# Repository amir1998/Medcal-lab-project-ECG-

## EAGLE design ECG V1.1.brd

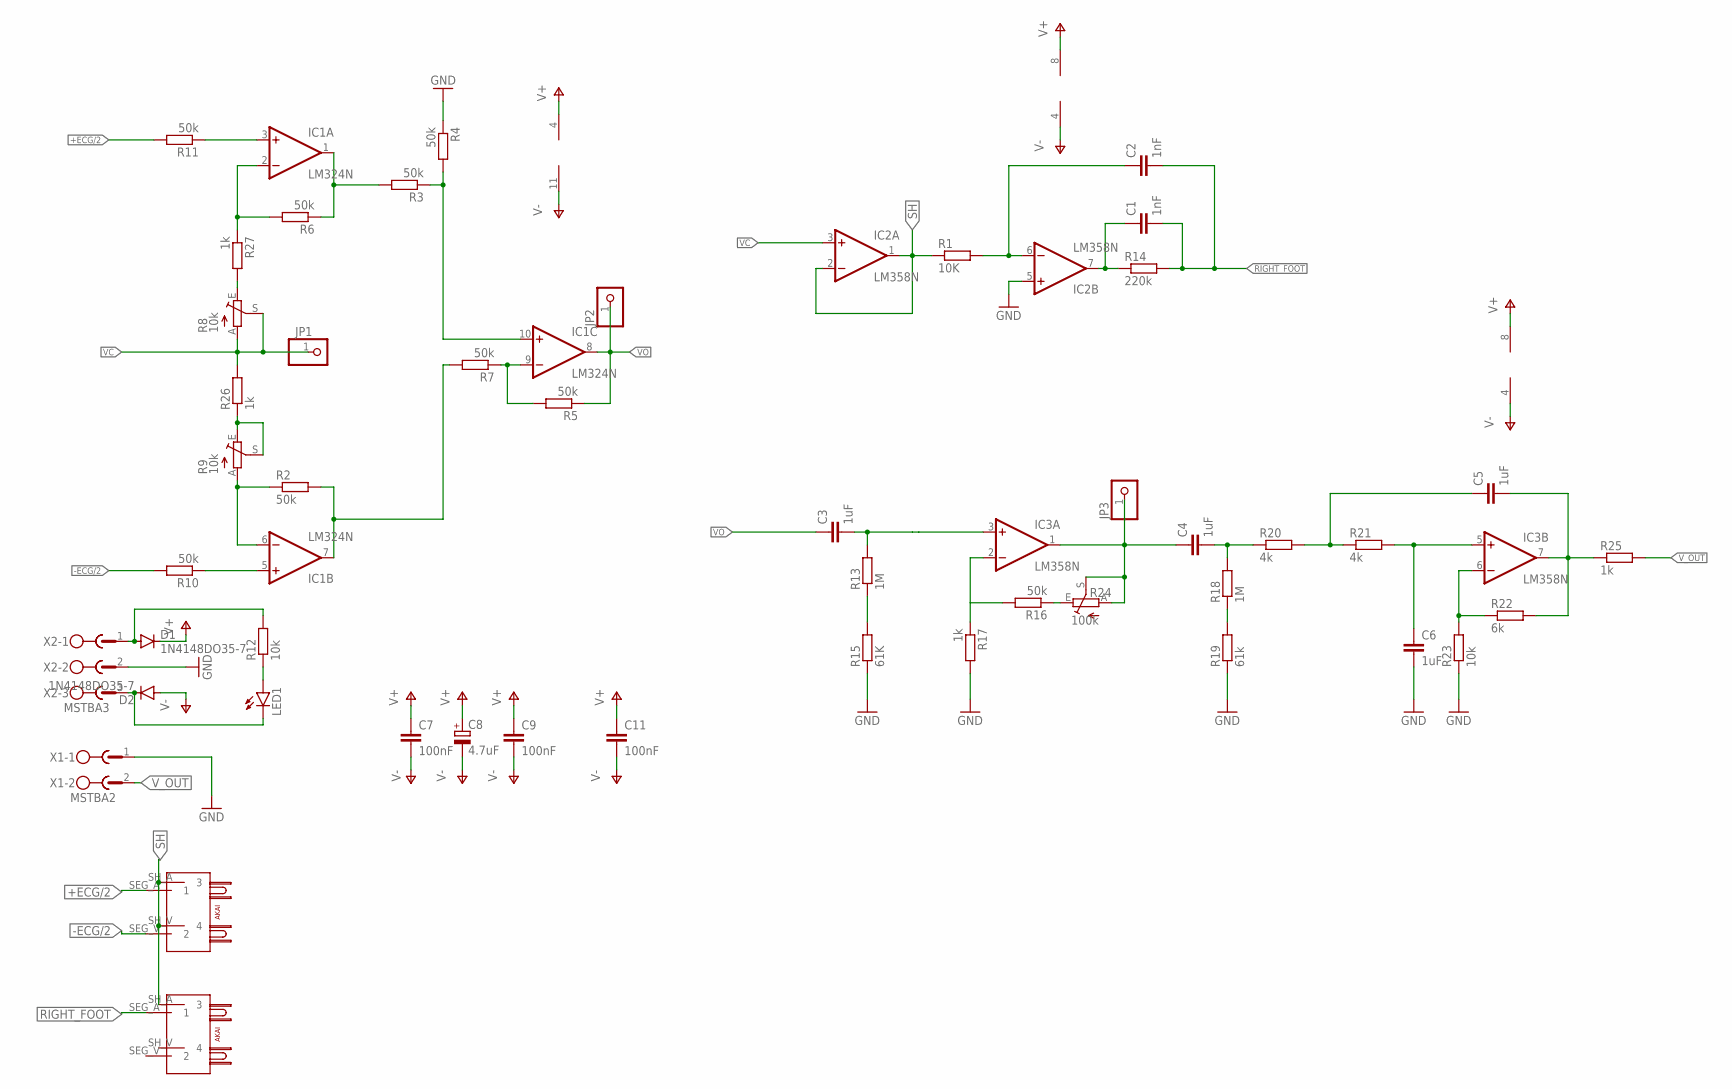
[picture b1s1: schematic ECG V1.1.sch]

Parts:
C1, C2: 1nF; C050-024X044
C3: 1uF; C075-032X103
C4, C5, C6: 1uF; C050-024X044
C7, C9, C11: 100nF; C050-024X044
C8: 4.7uF; E2-4
D1, D2: 1N4148DO35-7; DO35-7
IC1: LM324N; DIL14
IC2, IC3: LM358N; DIL08
JP1, JP2, JP3: PINHD-1X1; 1X01
LED1: LED3MM
R1: 10K; 0207/7
R2, R3, R4, R5, R6, R7, R10, R11, R16: 50k; 0207/7
R8, R9: 10k; S64W
R12, R23: 10k; 0207/7
R13, R18: 1M; 0207/7
R14: 220k; 0207/7
R15: 61K; 0207/7
R17, R25, R26, R27: 1k; 0207/7
R19: 61k; 0207/7
R20, R21: 4k; 0207/7
R22: 6k; 0207/7
R24: 100k; S64W
U$1, U$2: AKAI; DUAL_AKAI
X1: MSTBA2
X2: MSTBA3

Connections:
+ECG/2: R11.2, U$1.SEG_A (1)
-ECG/2: R10.2, U$1.SEG_V (2)
GND: C6.2, IC2.5 (+IN), R4.1, R15.1, R17.2, R19.1, R23.1, X1.1, X2.2
unnamed: IC1.1 (OUT), R3.2, R6.1
unnamed: IC1.6 (-IN), R2.1, R9.A
unnamed: IC1.7 (OUT), R2.2, R7.2
unnamed: IC1.2 (-IN), R6.2, R27.1
unnamed: IC1.10 (+IN), R3.1, R4.2
unnamed: IC1.9 (-IN), R5.2, R7.1
unnamed: R16.1, R24.E
unnamed: C3.2, IC3.3 (+IN), R13.2
unnamed: D2.C, LED1.K (C), X2.3
unnamed: C2.1, IC2.6 (-IN), R1.2
unnamed: C1.1, IC2.7 (OUT), R14.1
unnamed: R13.1, R15.2
unnamed: D1.A, R12.2, X2.1
unnamed: C4.1, IC3.1 (OUT), JP3.1, R24.A, R24.S
unnamed: IC3.2 (-IN), R16.2, R17.1
unnamed: C5.1, R20.2, R21.1
unnamed: R18.1, R19.2
unnamed: C4.2, R18.2, R20.1
unnamed: C6.1, IC3.5 (+IN), R21.2
unnamed: IC3.6 (-IN), R22.1, R23.2
unnamed: R8.E, R27.2
unnamed: IC1.5 (+IN), R10.1
unnamed: IC1.3 (+IN), R11.1
unnamed: LED1.A, R12.1
unnamed: R9.E, R9.S, R26.1
OUT: C5.2, IC3.7 (OUT), R22.2, R25.1
RIGHT_FOOT: C1.2, C2.2, R14.2, U$2.SEG_A (1)
SH: IC2.1 (OUT), IC2.2 (-IN), R1.1, U$1.SH_A (3), U$1.SH_V (4), U$2.SH_A (3)
V+: C7.1, C8.+, C9.1, C11.1, D1.C, IC1.4 (V+), IC2.8 (V+), IC3.8 (V+)
V-: C7.2, C8.-, C9.2, C11.2, D2.A, IC1.11 (V-), IC2.4 (V-), IC3.4 (V-)
VC: IC2.3 (+IN), JP1.1, R8.A, R8.S, R26.2
VO: C3.1, IC1.8 (OUT), JP2.1, R5.1
V_OUT: R25.2, X1.2

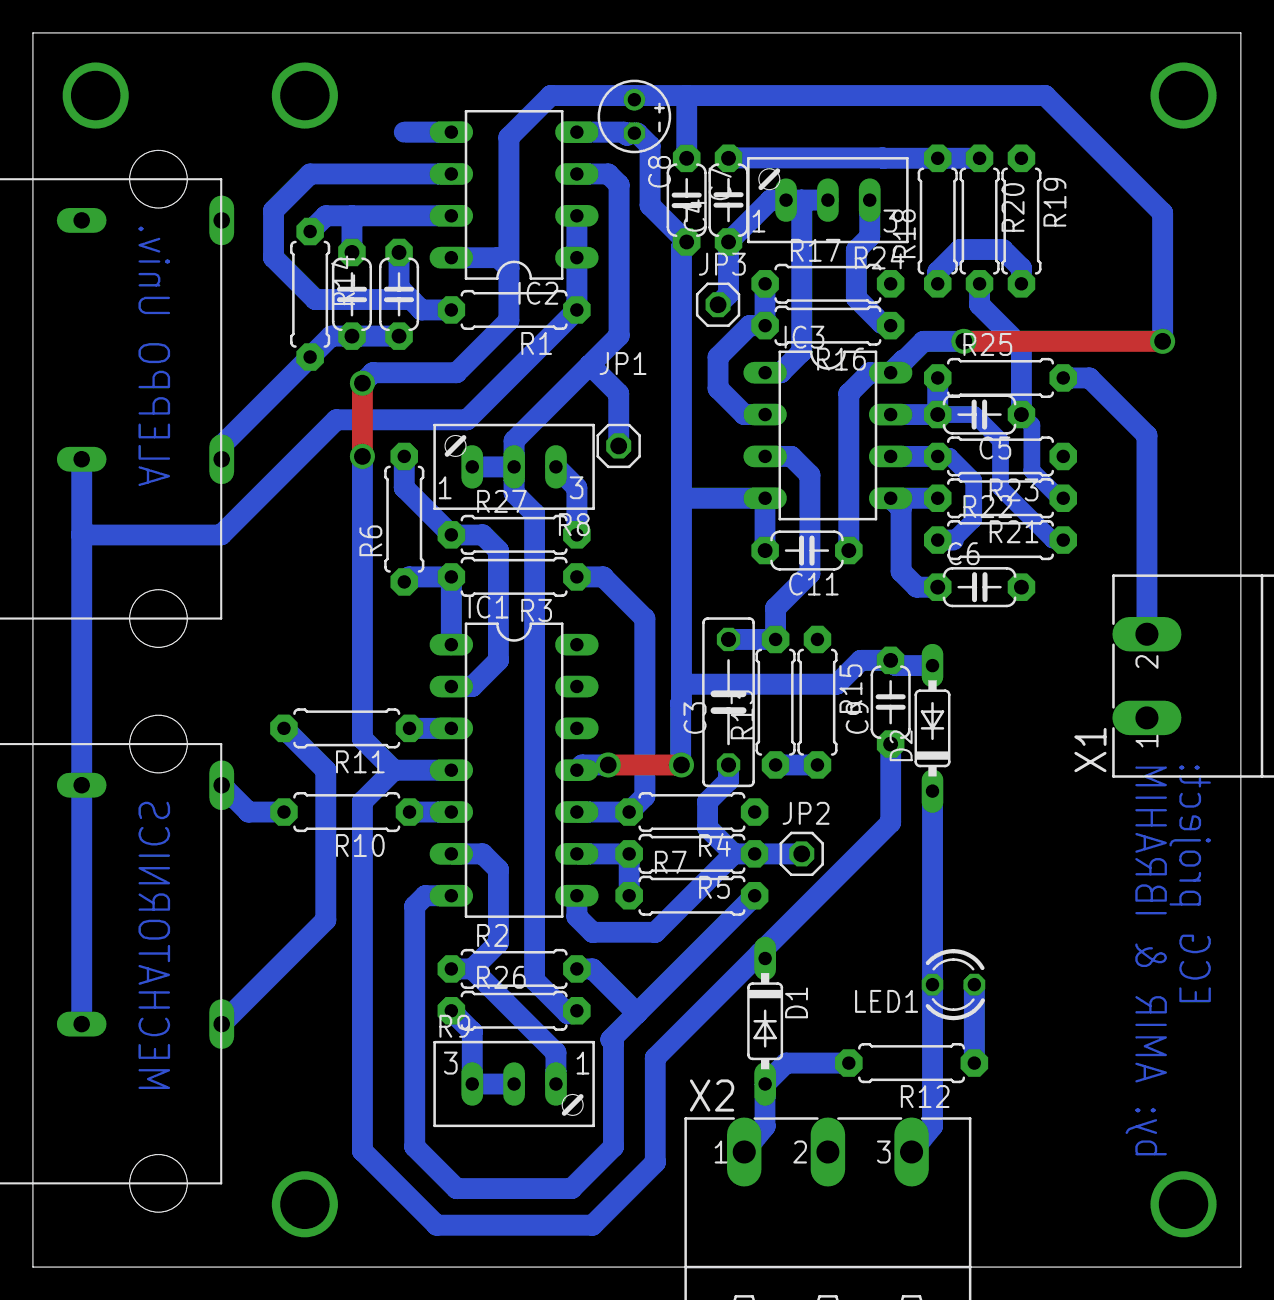
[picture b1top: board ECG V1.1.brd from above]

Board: 2 copper layers, 73.3 x 74.9 mm, 50 parts (0 on the bottom side), 36 nets.
